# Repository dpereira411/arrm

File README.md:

# Active Real Ring Modulator

This is a Kosmo format synth module based on Ken Stone's CGS [https://sdiy.info/wiki/CGS_active_real_ring_modulator](Active Real Ring Modulator). 

Main difference with Stone's original are:

* The instrument preamplifier was omitted
* Transformer footprints are for the TY-141P instead of the less available MO222
* Final stage input resistor is decreased to 10k, output resistor is increased to 1k, and a 100k pulldown is added on the output.

## Current draw
11.5 mA +12 V, 11.5 mA -12 V

## Photos

## Documentation

* [Schematic](Docs/arrm.pdf)
* PCB layout: [front](Docs/arrm_layout_front.pdf), [back](Docs/arrm_layout_back.pdf)
* [BOM](Docs/arrm_bom.md)
* [Build notes](Docs/build.md)
* [Blog post](https://analogoutputblog.wordpress.com/2022/05/05/cgs-ken-stone-active-real-ring-modulator/)

## GitHub repository

* [https://github.com/holmesrichards/arrm](https://github.com/holmesrichards/arrm)

## Submodules

This repo uses submodules aoKicad and Kosmo_panel, which provide needed libaries for KiCad. To clone:

```
git clone git@github.com:holmesrichards/arrm.git
git submodule init
git submodule update
```

Alternatively do

```
git clone --recurse-submodules git@github.com:holmesrichards/arrm.git
```

Or if you download the repository as a zip file, you must also click on the "aoKicad" and "Kosmo\_panel" links on the GitHub page (they'll have "@ something" after them) and download them as separate zip files which you can unzip into this repo's aoKicad and Kosmo\_panel directories.

If desired, copy the files from aoKicad and Kosmo\_panel to wherever you prefer (your KiCad user library directory, for instance, if you have one). Then in KiCad, go into Edit Symbols and add symbol libraries 

```
aoKicad/ao_symbols
Kosmo_panel/Kosmo
```
and go into Edit Footprints and add footprint libraries 
```
aoKicad/ao_tht
Kosmo_panel/Kosmo_panel.
```

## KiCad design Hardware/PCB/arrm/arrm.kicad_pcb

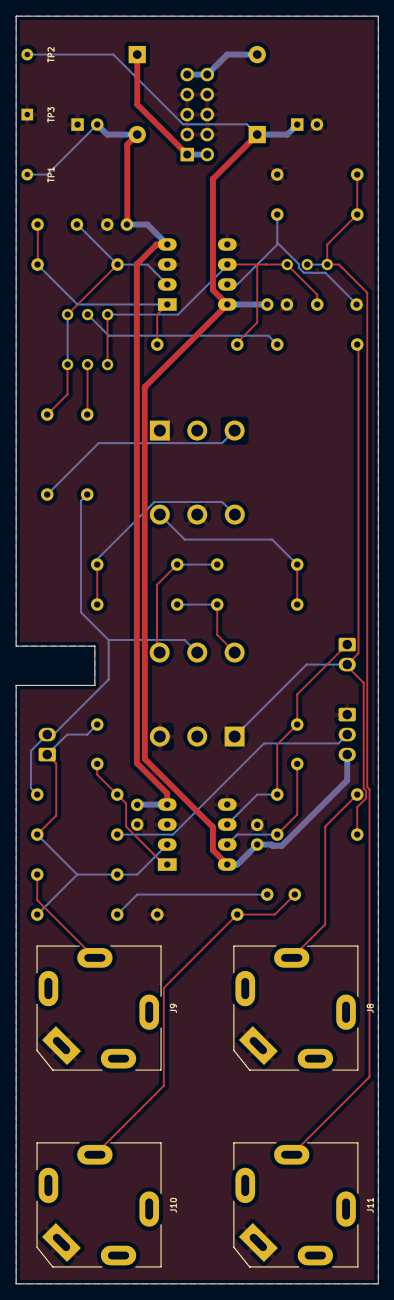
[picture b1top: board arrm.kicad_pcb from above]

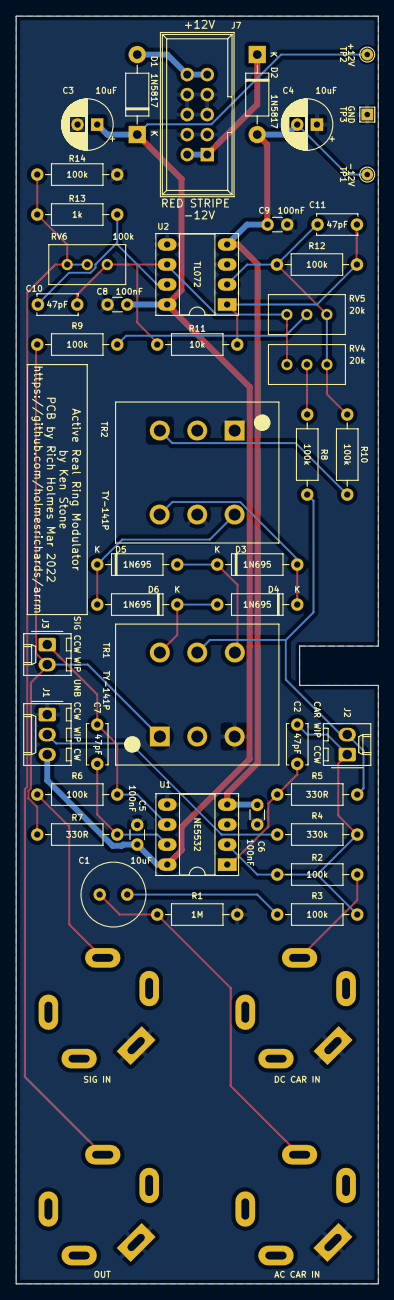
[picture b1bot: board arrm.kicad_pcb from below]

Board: 2 copper layers, 46.0 x 161.0 mm, 50 parts (45 on the bottom side), 28 nets.

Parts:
C1: 10uF; C_Radial_D8.0mm_H11.5mm_P3.50mm
C2, C7, C10, C11: 47pF; C_Disc_D5.0mm_W2.5mm_P5.00mm
C3, C4: 10uF; CP_Radial_D6.3mm_P2.50mm
C5, C6, C8, C9: 100nF; C_Disc_D3.0mm_W1.6mm_P2.50mm
D1, D2: 1N5817; D_DO-41_SOD81_P10.16mm_Horizontal
D3, D4, D5, D6: 1N695; D_DO-7_P10.16mm_Horizontal
GRAF1: Holes; ringmod_panel_2_holes
J1: 3_pin_Molex_header; Molex_KK-254_AE-6410-03A_1x03_P2.54mm_Vertical
J2, J3: 2_pin_Molex_header; Molex_KK-254_AE-6410-02A_1x02_P2.54mm_Vertical
J7: Synth_power_2x5; Power_Header
J8, J9, J10, J11: AudioJack2; Jack_6.35mm_PJ_629HAN_slots
R1: 1M; R_Axial_DIN0207_L6.3mm_D2.5mm_P10.16mm_Horizontal
R2, R3, R6, R8, R9, R10, R12, R14: 100k; R_Axial_DIN0207_L6.3mm_D2.5mm_P10.16mm_Horizontal
R4: 330k; R_Axial_DIN0207_L6.3mm_D2.5mm_P10.16mm_Horizontal
R5, R7: 330R; R_Axial_DIN0207_L6.3mm_D2.5mm_P10.16mm_Horizontal
R11: 10k; R_Axial_DIN0207_L6.3mm_D2.5mm_P10.16mm_Horizontal
R13: 1k; R_Axial_DIN0207_L6.3mm_D2.5mm_P10.16mm_Horizontal
RV4, RV5: 20k; Potentiometer_Bourns_3296W_Vertical_standard
RV6: 100k; Potentiometer_Bourns_3296W_Vertical_standard
TP1: -12V; TestPoint_THTPad_D1.5mm_Drill0.7mm
TP2: +12V; TestPoint_THTPad_D1.5mm_Drill0.7mm
TP3: GND; TestPoint_THTPad_1.5x1.5mm_Drill0.7mm
TR1, TR2: TY-141P; Transformer_TY-141P
U1: NE5532; DIP-8_W7.62mm_Socket_LongPads
U2: TL072; DIP-8_W7.62mm_Socket_LongPads

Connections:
+12V: C3.1, C5.1, C8.1, D1.1 (K), J1.3, TP2.1, U1.8 (V+), U2.8 (V+)
-12V: C4.2, C6.2, C9.2, D2.2 (A), TP1.1, U1.4 (V-), U2.4 (V-)
/Main PCB/+12_IN: D1.2 (A), J7.9 (+12V), J7.10 (+12V)
/Main PCB/-12_IN: D2.1 (K), J7.1 (-12V), J7.2 (-12V)
/Main PCB/AC CARR IN: C1.2, J10.T, R1.1
/Main PCB/CARRLVL_CCW: C2.1, J2.1, R2.2, R3.2, R4.2, U1.2 (-)
/Main PCB/CARRLVL_WIP: J2.2, R5.2, R8.1, TR1.5
/Main PCB/CNULL: R8.2, RV4.2
/Main PCB/DC CARR IN: J9.T, R2.1
/Main PCB/OUT: J11.T, R13.2, R14.2, RV6.2, RV6.3
/Main PCB/SIG IN: J8.T, R6.1
/Main PCB/SIGLVL_CCW: C7.1, J3.1, R6.2, U1.6 (-)
/Main PCB/SIGLVL_WIP: J3.2, R7.2, R9.1, TR1.1
/Main PCB/SNULL: R9.2, RV5.2
/Main PCB/UNBAL_WIP: J1.2, R4.1
GND: C3.2, C4.1, C5.2, C6.1, C8.2, C9.1, J1.1, J7.3 (GND), J7.4 (GND), J7.5 (GND), J7.6 (GND), J7.7 (GND), J7.8 (GND), J8.S, J9.S, J10.S, J11.S, R1.2, R14.1, TP3.1, TR1.3, TR2.1, TR2.5, U1.3 (+), U1.5 (+), U2.3 (+), U2.5 (+)
unnamed: C1.1, R3.1
unnamed: C2.2, R5.1, U1.1
unnamed: C7.2, R7.1, U1.7
unnamed: C10.1, R11.2, RV4.1, RV5.1, RV6.1, U2.6 (-)
unnamed: C10.2, R13.1, U2.7
unnamed: C11.1, R10.2, R12.1, RV4.3, RV5.3, U2.2 (-)
unnamed: C11.2, R11.1, R12.2, U2.1
unnamed: D3.1 (K), D5.2 (A), TR1.4
unnamed: D3.2 (A), D4.1 (K), TR2.4
unnamed: D4.2 (A), D6.1 (K), TR1.6
unnamed: D5.1 (K), D6.2 (A), TR2.6
unnamed: R10.1, TR2.3

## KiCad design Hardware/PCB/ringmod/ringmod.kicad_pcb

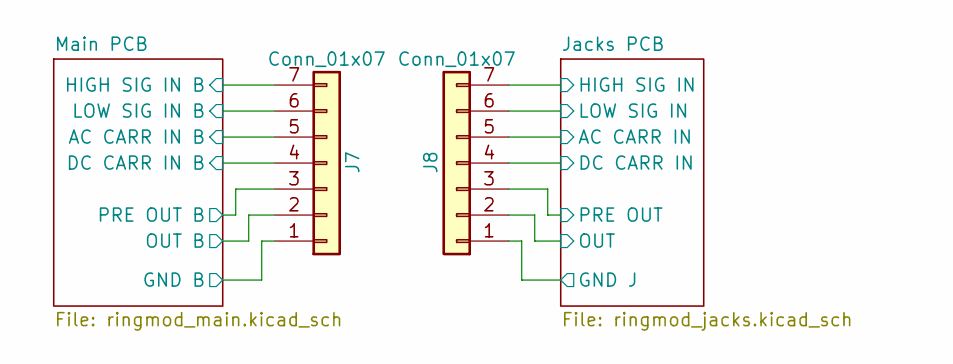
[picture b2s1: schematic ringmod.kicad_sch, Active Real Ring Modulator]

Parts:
J7: Conn_01x07; PinSocket_1x07_P2.54mm_Vertical
J8: Conn_01x07; PinHeader_1x07_P2.54mm_Vertical

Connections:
/Jacks PCB/AC CARR IN: J8.5; also elsewhere on the board
/Jacks PCB/DC CARR IN: J8.4; also elsewhere on the board
/Jacks PCB/HIGH SIG IN: J8.7; also elsewhere on the board
/Jacks PCB/LOW SIG IN: J8.6; also elsewhere on the board
/Jacks PCB/OUT: J8.2; also elsewhere on the board
/Jacks PCB/PRE OUT: J8.3; also elsewhere on the board
/Main PCB/AC CARR IN B: J7.5; also elsewhere on the board
/Main PCB/DC CARR IN B: J7.4; also elsewhere on the board
/Main PCB/HIGH SIG IN B: J7.7; also elsewhere on the board
/Main PCB/LOW SIG IN B: J7.6; also elsewhere on the board
/Main PCB/OUT B: J7.2; also elsewhere on the board
/Main PCB/PRE OUT B: J7.3; also elsewhere on the board
GND: J7.1; also elsewhere on the board
GND1: J8.1; also elsewhere on the board

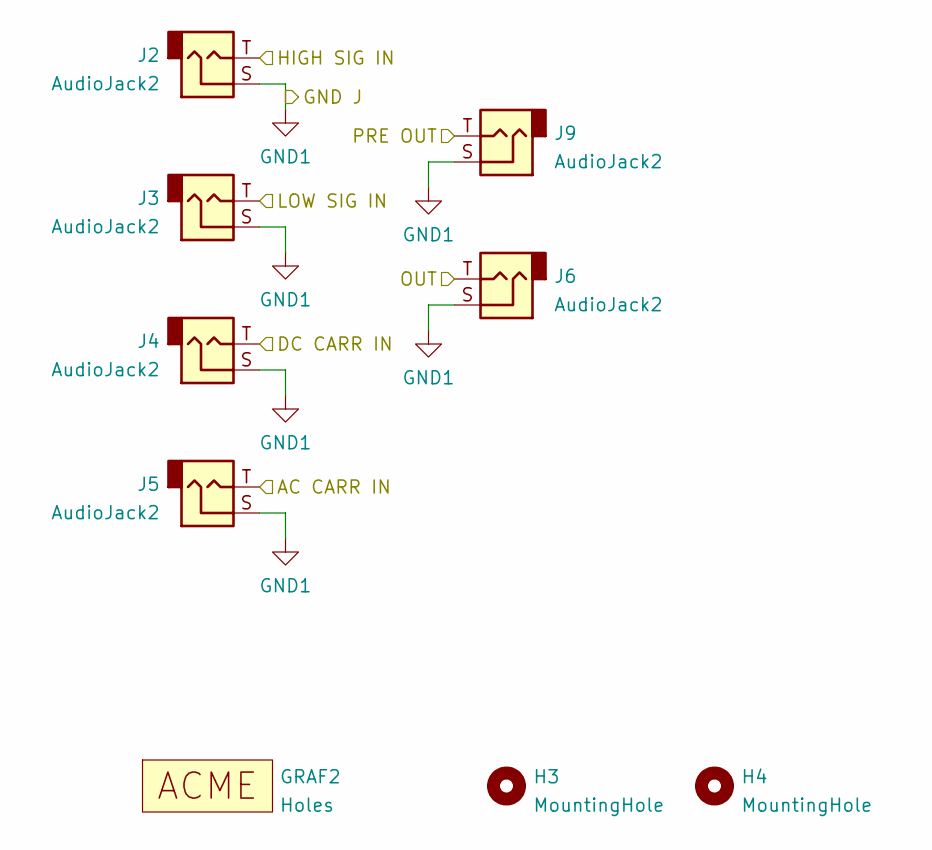
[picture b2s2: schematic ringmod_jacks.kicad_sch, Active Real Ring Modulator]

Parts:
GRAF2: Holes; ringmod_panel_holes
H3, H4: MountingHole; MountingHole_3.2mm_M3
J2, J3, J4, J5, J6, J9: AudioJack2; Jack_6.35mm_PJ_629HAN_slots

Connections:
/Jacks PCB/AC CARR IN: J5.T; also elsewhere on the board
/Jacks PCB/DC CARR IN: J4.T; also elsewhere on the board
/Jacks PCB/HIGH SIG IN: J2.T; also elsewhere on the board
/Jacks PCB/LOW SIG IN: J3.T; also elsewhere on the board
/Jacks PCB/OUT: J6.T; also elsewhere on the board
/Jacks PCB/PRE OUT: J9.T; also elsewhere on the board
GND1: J2.S, J3.S, J4.S, J5.S, J6.S, J9.S; also elsewhere on the board

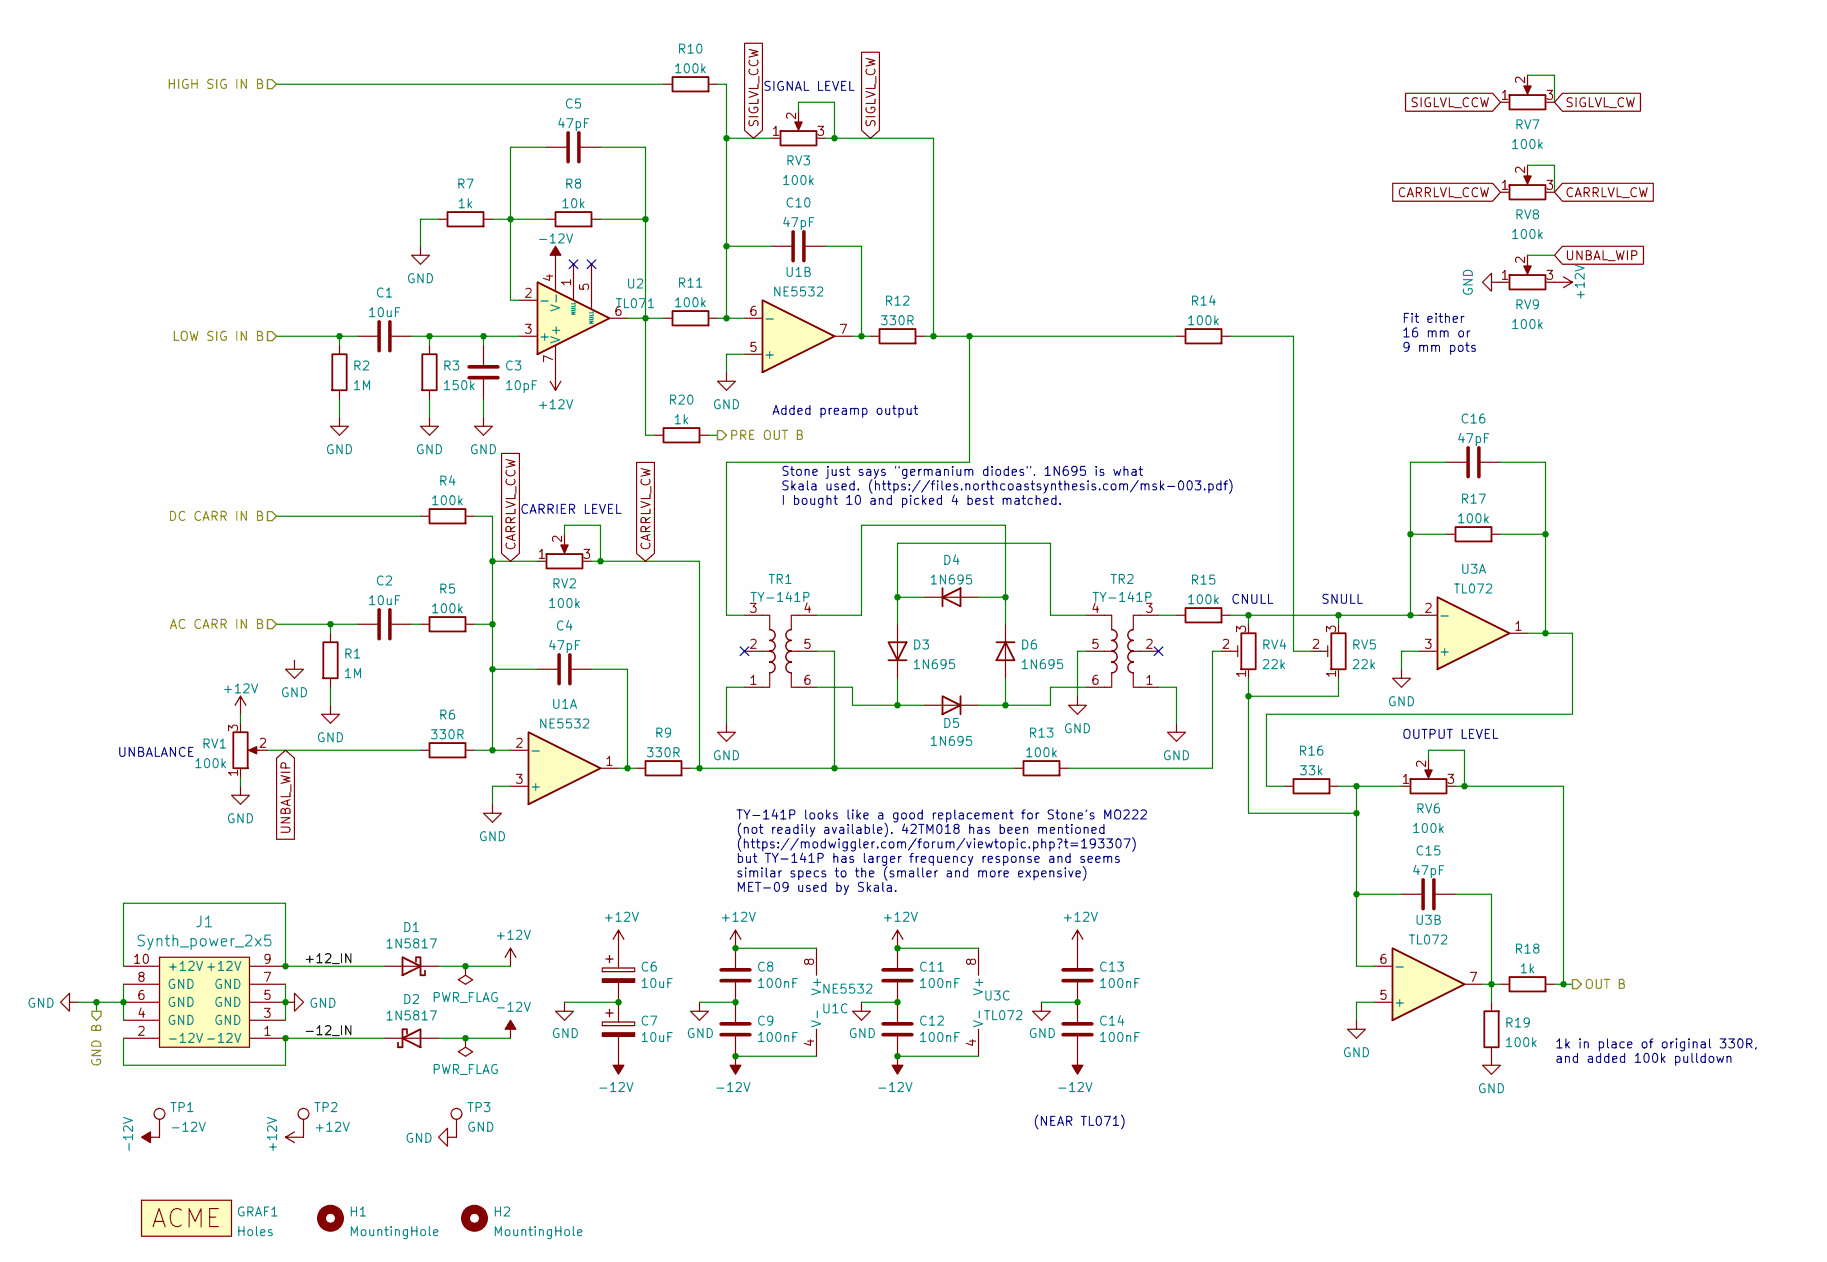
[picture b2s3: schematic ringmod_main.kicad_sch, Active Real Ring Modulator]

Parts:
C1, C2: 10uF; C_Radial_D6.3mm_H11.0mm_P2.50mm
C3: 10pF; C_Disc_D3.0mm_W1.6mm_P2.50mm
C4, C5, C10, C15, C16: 47pF; C_Disc_D3.0mm_W1.6mm_P2.50mm
C6, C7: 10uF; CP_Radial_D6.3mm_P2.50mm
C8, C9, C11, C12, C13, C14: 100nF; C_Disc_D3.0mm_W1.6mm_P2.50mm
D1, D2: 1N5817; D_DO-41_SOD81_P10.16mm_Horizontal
D3, D4, D5, D6: 1N695; D_DO-7_P10.16mm_Horizontal
GRAF1: Holes; ringmod_panel_holes
H1, H2: MountingHole; MountingHole_3.2mm_M3
J1: Synth_power_2x5; Power_Header
R1, R2: 1M; R_Axial_DIN0207_L6.3mm_D2.5mm_P10.16mm_Horizontal
R3: 150k; R_Axial_DIN0207_L6.3mm_D2.5mm_P10.16mm_Horizontal
R4, R5, R10, R11, R13, R14, R15, R17, R19: 100k; R_Axial_DIN0207_L6.3mm_D2.5mm_P10.16mm_Horizontal
R6, R9, R12: 330R; R_Axial_DIN0207_L6.3mm_D2.5mm_P10.16mm_Horizontal
R7, R18, R20: 1k; R_Axial_DIN0207_L6.3mm_D2.5mm_P10.16mm_Horizontal
R8: 10k; R_Axial_DIN0207_L6.3mm_D2.5mm_P10.16mm_Horizontal
R16: 33k; R_Axial_DIN0207_L6.3mm_D2.5mm_P10.16mm_Horizontal
RV1, RV2, RV3: 100k; Potentiometer_Alpha_16mm_Single_Vertical
RV4, RV5: 22k; Potentiometer_Bourns_3296W_Vertical_standard
RV6: 100k; Potentiometer_Bourns_3296W_Vertical_standard
RV7, RV8, RV9: 100k; Potentiometer_Alpha_RD901F-40-00D_Single_Vertical_centered
TP1: -12V; TestPoint_THTPad_D1.5mm_Drill0.7mm
TP2: +12V; TestPoint_THTPad_D1.5mm_Drill0.7mm
TP3: GND; TestPoint_THTPad_1.5x1.5mm_Drill0.7mm
TR1, TR2: TY-141P; Transformer_TY-141P
U1: NE5532; DIP-8_W7.62mm_Socket_LongPads
U2: TL071; DIP-8_W7.62mm_Socket_LongPads
U3: TL072; DIP-8_W7.62mm_Socket_LongPads

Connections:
+12V: C6.1, C8.1, C11.1, C13.1, D1.1 (K), RV1.3, RV9.3, TP2.1, U1.8 (V+), U2.7 (V+), U3.8 (V+)
-12V: C7.2, C9.2, C12.2, C14.2, D2.2 (A), TP1.1, U1.4 (V-), U2.4 (V-), U3.4 (V-)
/Main PCB/+12_IN: D1.2 (A), J1.9 (+12V), J1.10 (+12V)
/Main PCB/-12_IN: D2.1 (K), J1.1 (-12V), J1.2 (-12V)
/Main PCB/AC CARR IN B: C2.2, R1.1; also elsewhere on the board
/Main PCB/DC CARR IN B: R4.1; also elsewhere on the board
/Main PCB/HIGH SIG IN B: R10.1; also elsewhere on the board
/Main PCB/LOW SIG IN B: C1.2, R2.1; also elsewhere on the board
/Main PCB/OUT B: R18.2, RV6.2, RV6.3; also elsewhere on the board
/Main PCB/PRE OUT B: R20.2; also elsewhere on the board
CARRLVL_CCW: C4.1, R4.2, R5.2, R6.2, RV2.1, RV8.1, U1.2 (-)
CARRLVL_CW: R9.2, R13.1, RV2.2, RV2.3, RV8.2, RV8.3, TR1.5
GND: C3.1, C6.2, C7.1, C8.2, C9.1, C11.2, C12.1, C13.2, C14.1, J1.3 (GND), J1.4 (GND), J1.5 (GND), J1.6 (GND), J1.7 (GND), J1.8 (GND), R1.2, R2.2, R3.2, R7.1, R19.1, RV1.1, RV9.1, TP3.1, TR1.1, TR2.1, TR2.5, U1.3 (+), U1.5 (+), U3.3 (+), U3.5 (+); also elsewhere on the board
unnamed: C1.1, C3.2, R3.1, U2.3 (+)
unnamed: C2.1, R5.1
unnamed: C4.2, R9.1, U1.1
unnamed: C5.1, R7.2, R8.1, U2.2 (-)
unnamed: C5.2, R8.2, R11.1, R20.1, U2.6
unnamed: C10.2, R12.1, U1.7
unnamed: C15.1, R16.2, RV4.1, RV5.1, RV6.1, U3.6 (-)
unnamed: C15.2, R18.1, R19.2, U3.7
unnamed: C16.1, R15.2, R17.1, RV4.3, RV5.3, U3.2 (-)
unnamed: C16.2, R16.1, R17.2, U3.1
unnamed: D3.1 (K), D5.2 (A), TR1.6
unnamed: D3.2 (A), D4.1 (K), TR2.4
unnamed: D4.2 (A), D6.1 (K), TR1.4
unnamed: D5.1 (K), D6.2 (A), TR2.6
unnamed: R13.2, RV4.2
unnamed: R14.2, RV5.2
unnamed: R15.1, TR2.3
SIGLVL_CCW: C10.1, R10.2, R11.2, RV3.1, RV7.1, U1.6 (-)
SIGLVL_CW: R12.2, R14.1, RV3.2, RV3.3, RV7.2, RV7.3, TR1.3
UNBAL_WIP: R6.1, RV1.2, RV9.2

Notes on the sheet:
CNULL
OUTPUT LEVEL
CARRIER LEVEL
1k in place of original 330R, and added 100k pulldown
Stone just says "germanium diodes". 1N695 is what Skala used. (https://files.northcoastsynthesis.com/msk-003.pdf) I bought 10 and picked 4 best matched.
Fit either 16 mm or 9 mm pots
SNULL
TY-141P looks like a good replacement for Stone's MO222 (not readily available). 42TM018 has been mentioned (https://modwiggler.com/forum/viewtopic.php?t=193307) but TY-141P has larger frequency response and seems similar specs to the (smaller and more expensive) MET-09 used by Skala.
SIGNAL LEVEL
(NEAR TL071)
UNBALANCE
Added preamp output

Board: 2 copper layers, 74 parts (52 on the bottom side), 40 nets, no tracks yet.

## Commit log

2021-11-24 Initial version
2021-11-25 Update pot symbols
2021-12-05 Panel art
2021-12-11 .gitignore, fix pot symbols
2021-12-22 remove inst preamp, redesign panel
2021-12-25 README
2022-02-01 rm first design; add new holes image
2022-03-12 Layout revision
2022-03-19 Rename project; reduce input resistor on output stage
2022-03-21 Rename project, cleanup
2022-03-21 Panel
2022-03-22 rm ARRM.md; add to README.md
2022-05-03 Final pre fab tweaks, Gerbers
2022-05-03 Fix footprint path; fix transformer footprint
2022-05-05 Post fab updates
2022-05-05 Docs, pics, new Gerbers
2022-05-05 R4 should be 330k
2022-05-06 fix bad link
2022-05-09 Blog post
2022-05-23 Current draw
2022-06-05 Also fix schematic R4
